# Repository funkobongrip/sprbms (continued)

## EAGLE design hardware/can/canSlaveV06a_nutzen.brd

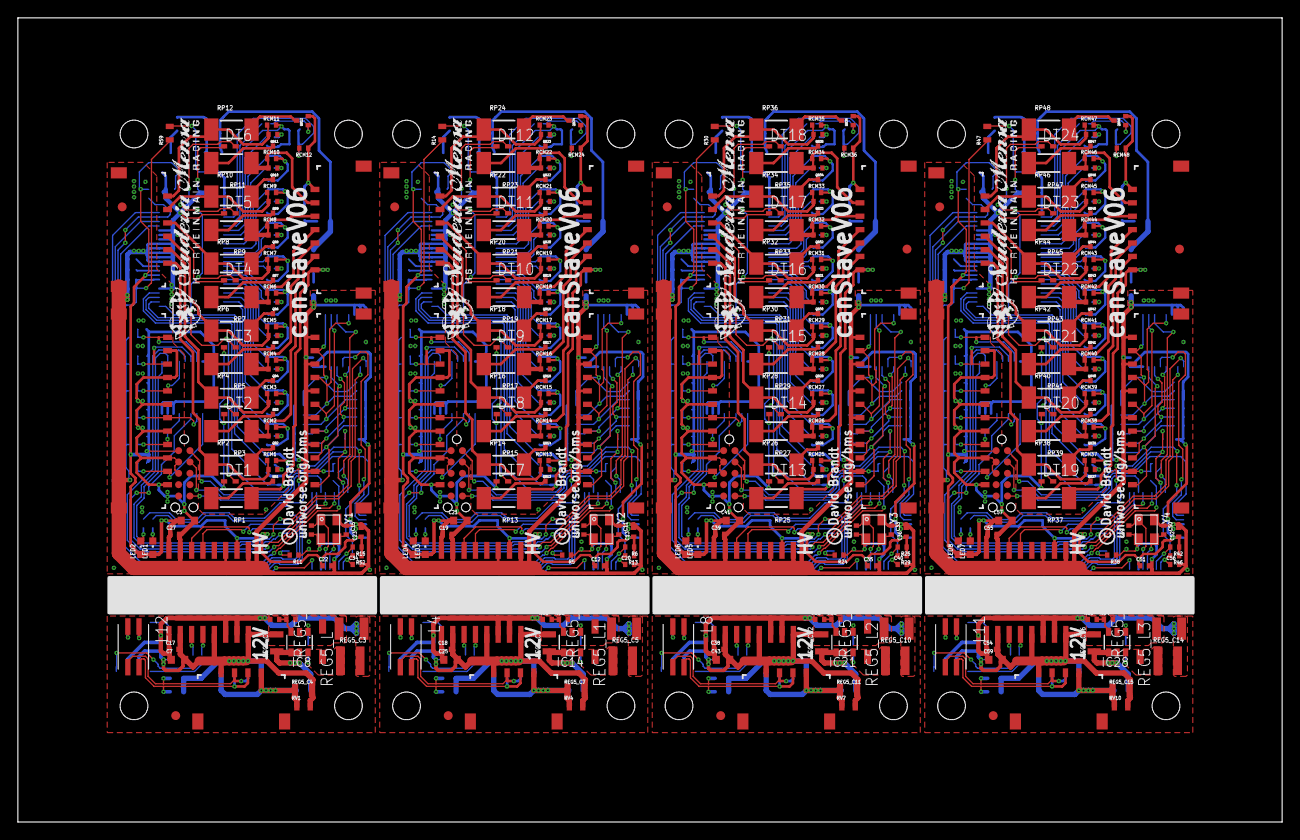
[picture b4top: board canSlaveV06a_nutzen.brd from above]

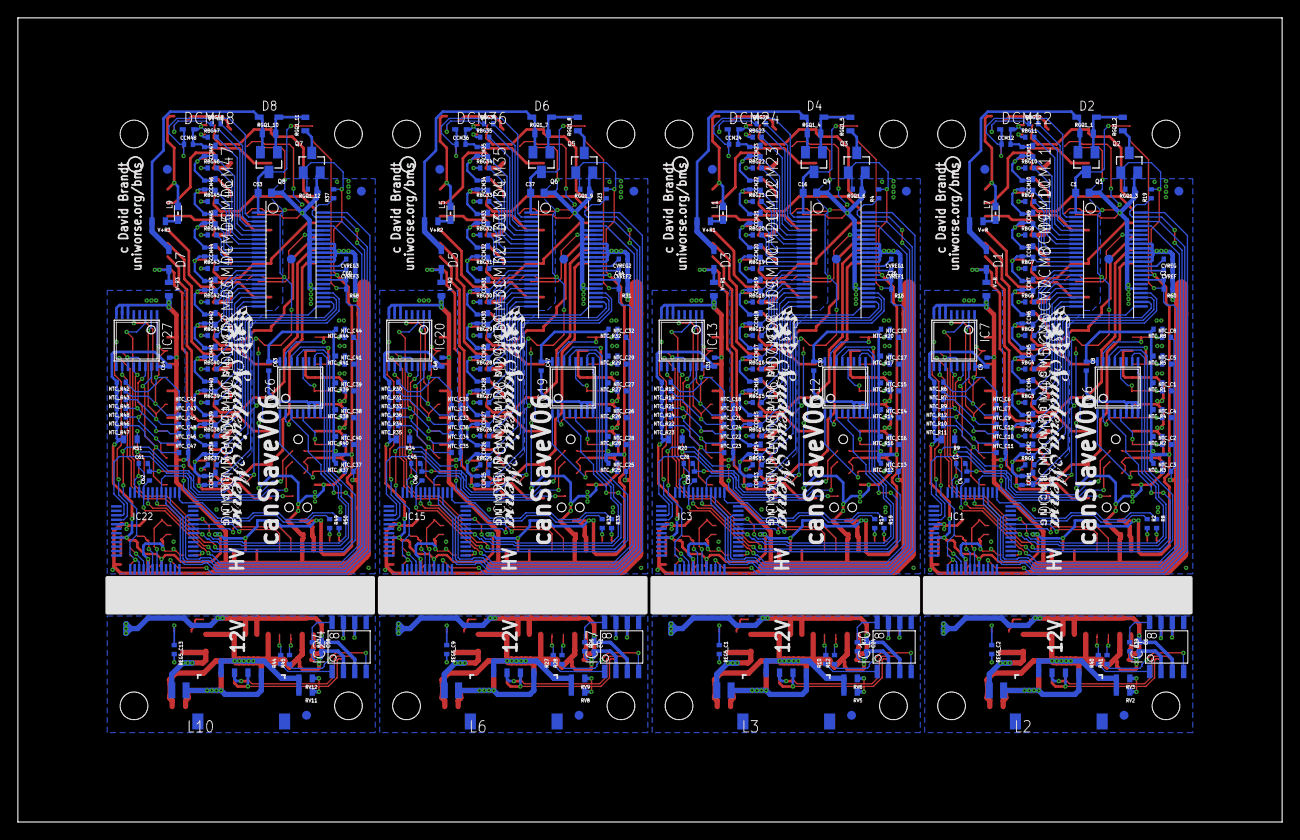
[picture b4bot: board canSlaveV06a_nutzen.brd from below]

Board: 2 copper layers, 141.5 x 90.0 mm, 724 parts (404 on the bottom side), 492 nets.

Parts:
C1, C16, C37, C53: 100n,100V; C0603
C2, C3, C4, C12, C13, C20, C22, C23, C26, C28, C29, C34, C35, C36, C40, C44, C45, C46, C51, C52, C56, C60, C61, C62: 100n; C0402
C5, C7, C21, C25, C41, C43, C57, C59: 10u,10V,X7R; C0603
C6, C8, C9, C17, C18, C19, C24, C27, C30, C31, C38, C39, C42, C47, C48, C54, C55, C58, C63, C64: 100n,>10V,X7R; C0402
C10, C11, C14, C15, C32, C33, C49, C50: 10p; C0402
CCM1, CCM2, CCM3, CCM4, CCM5, CCM6, CCM7, CCM8, CCM9, CCM10, CCM11, CCM12, CCM13, CCM14, CCM15, CCM16, CCM17, CCM18, CCM19, CCM20, CCM21, CCM22, CCM23, CCM24, CCM25, CCM26, CCM27, CCM28, CCM29, CCM30, CCM31, CCM32, CCM33, CCM34, CCM35, CCM36, CCM37, CCM38, CCM39, CCM40, CCM41, CCM42, CCM43, CCM44, CCM45, CCM46, CCM47, CCM48: 100n; C0402
CVREF, CVREF1, CVREF2, CVREF3: 1u; C0402
CVREG, CVREG1, CVREG2, CVREG3: 1u; C0402
D1, D3, D5, D7: 51V; SOD323-L
D2, D4, D6, D8: 12V; SOD323-L
DBG1, DBG2, DBG3, DBG4: JTAG10-TC2050-NL; TC2050-NL-JTORDER
DCM1, DCM2, DCM3, DCM4, DCM5, DCM6, DCM7, DCM8, DCM9, DCM10, DCM11, DCM12, DCM13, DCM14, DCM15, DCM16, DCM17, DCM18, DCM19, DCM20, DCM21, DCM22, DCM23, DCM24, DCM25, DCM26, DCM27, DCM28, DCM29, DCM30, DCM31, DCM32, DCM33, DCM34, DCM35, DCM36, DCM37, DCM38, DCM39, DCM40, DCM41, DCM42, DCM43, DCM44, DCM45, DCM46, DCM47, DCM48: 7.5; SOD523
DT1, DT2, DT3, DT4, DT5, DT6, DT7, DT8, DT9, DT10, DT11, DT12, DT13, DT14, DT15, DT16, DT17, DT18, DT19, DT20, DT21, DT22, DT23, DT24: 1PS79SB40; SOD523
FID1, FID2, FID3, FID4, FID5, FID6, FID7, FID8, FID9, FID10, FID11, FID12, FID13, FID14, FID15, FID16, FID17, FID18, FID19, FID20, FID21, FID22, FID23, FID24, FID25, FID26, FID27, FID28: FIDUCIAL""; FIDUCIAL_1MM
IC1, IC3, IC15, IC22: LPC11C14; LQFP48
IC2, IC9, IC16, IC23: LTC6803-4; 44SSOP
IC4, IC10, IC17, IC24: PCA82C251; SO-8
IC5, IC11, IC18, IC25: ADUM5201; SO16WB
IC6, IC7, IC12, IC13, IC19, IC20, IC26, IC27: 4052-TSSOP16; TSSOP16
IC8, IC14, IC21, IC28: LMR14203; SOT23-6
L1, L5, L7, L9: WE-CBF,742792664; 0603
L2, L3, L6, L10: WE-PMI/74479776233A; WE-PMI_0806
L4, L8, L11, L12: 744242101; WE-SLM
LED1, LED3, LED5, LED7: GRN; CHIPLED_0603
LED2, LED4, LED6, LED8: RED; CHIPLED_0603
NTC_C1, NTC_C2, NTC_C3, NTC_C4, NTC_C5, NTC_C6, NTC_C7, NTC_C8, NTC_C9, NTC_C10, NTC_C11, NTC_C12, NTC_C13, NTC_C14, NTC_C15, NTC_C16, NTC_C17, NTC_C18, NTC_C19, NTC_C20, NTC_C21, NTC_C22, NTC_C23, NTC_C24, NTC_C25, NTC_C26, NTC_C27, NTC_C28, NTC_C29, NTC_C30, NTC_C31, NTC_C32, NTC_C33, NTC_C34, NTC_C35, NTC_C36, NTC_C37, NTC_C38, NTC_C39, NTC_C40, NTC_C41, NTC_C42, NTC_C43, NTC_C44, NTC_C45, NTC_C46, NTC_C47, NTC_C48: 1u; C0402
NTC_R1, NTC_R2, NTC_R3, NTC_R4, NTC_R5, NTC_R6, NTC_R7, NTC_R8, NTC_R9, NTC_R10, NTC_R11, NTC_R12, NTC_R13, NTC_R14, NTC_R15, NTC_R16, NTC_R17, NTC_R18, NTC_R19, NTC_R20, NTC_R21, NTC_R22, NTC_R23, NTC_R24, NTC_R25, NTC_R26, NTC_R27, NTC_R28, NTC_R29, NTC_R30, NTC_R31, NTC_R32, NTC_R33, NTC_R34, NTC_R35, NTC_R36, NTC_R37, NTC_R38, NTC_R39, NTC_R40, NTC_R41, NTC_R42, NTC_R43, NTC_R44, NTC_R45, NTC_R46, NTC_R47, NTC_R48: 10k; R0402
Q1, Q4, Q6, Q8: BSS84; SOT23
Q2, Q3, Q5, Q7: 2N7002; SOT23
QB1, QB2, QB3, QB4, QB5, QB6, QB7, QB8, QB9, QB10, QB11, QB12, QB13, QB14, QB15, QB16, QB17, QB18, QB19, QB20, QB21, QB22, QB23, QB24, QB25, QB26, QB27, QB28, QB29, QB30, QB31, QB32, QB33, QB34, QB35, QB36, QB37, QB38, QB39, QB40, QB41, QB42, QB43, QB44, QB45, QB46, QB47, QB48: BSS84AKT; SOT416
R1, R21, R35, R53: 5.62k; R0402
R2, R8, R17, R18, R32, R33, R49, R50: 1k; R0402
R3, R22, R36, R54: 1.02k; R0402
R4, R19, R23, R37: 4.7k; R0402
R5, R6, R11, R13, R15, R24, R25, R29, R38, R42, R46, R52: 10k; R0402
R7, R26, R39, R43: 0; R0402
R9, R20, R34, R51: 3.3k; R0603
R10, R12, R27, R28, R40, R41, R44, R45: 100; R0402
R14, R30, R47, R59: 332k0.1%; R0603
R16, R31, R48, R60: 20k0.1%; R0402
RBG1, RBG2, RBG3, RBG4, RBG5, RBG6, RBG7, RBG8, RBG9, RBG10, RBG11, RBG12, RBG13, RBG14, RBG15, RBG16, RBG17, RBG18, RBG19, RBG20, RBG21, RBG22, RBG23, RBG24, RBG25, RBG26, RBG27, RBG28, RBG29, RBG30, RBG31, RBG32, RBG33, RBG34, RBG35, RBG36, RBG37, RBG38, RBG39, RBG40, RBG41, RBG42, RBG43, RBG44, RBG45, RBG46, RBG47, RBG48: 3.3k; R0402
RCM1, RCM2, RCM3, RCM4, RCM5, RCM6, RCM7, RCM8, RCM9, RCM10, RCM11, RCM12, RCM13, RCM14, RCM15, RCM16, RCM17, RCM18, RCM19, RCM20, RCM21, RCM22, RCM23, RCM24, RCM25, RCM26, RCM27, RCM28, RCM29, RCM30, RCM31, RCM32, RCM33, RCM34, RCM35, RCM36, RCM37, RCM38, RCM39, RCM40, RCM41, RCM42, RCM43, RCM44, RCM45, RCM46, RCM47, RCM48: 100; R0402
REG5_C1, REG5_C2, REG5_C9, REG5_C13: 100n,>=25V,>=X5R; C0402
REG5_C3, REG5_C5, REG5_C10, REG5_C14: 47u,10V,X7R; C1210
REG5_C4, REG5_C6, REG5_C7, REG5_C8, REG5_C11, REG5_C12, REG5_C15, REG5_C16: 2.2u,50V,X7R; C0805
REG5_D1, REG5_D2, REG5_D3, REG5_D4: PMEG6010CEH; SOD123
REG5_L, REG5_L1, REG5_L2, REG5_L3: 744025100; WE-TPC_2828
RGQ1_1, RGQ1_4, RGQ1_7, RGQ1_10: 1M,50V; R0603
RGQ1_2, RGQ1_5, RGQ1_8, RGQ1_11: 100k,50V; R0603
RGQ1_3, RGQ1_6, RGQ1_9, RGQ1_12: 1M; R0402
RP1, RP2, RP3, RP4, RP5, RP6, RP7, RP8, RP9, RP10, RP11, RP12, RP13, RP14, RP15, RP16, RP17, RP18, RP19, RP20, RP21, RP22, RP23, RP24, RP25, RP26, RP27, RP28, RP29, RP30, RP31, RP32, RP33, RP34, RP35, RP36, RP37, RP38, RP39, RP40, RP41, RP42, RP43, RP44, RP45, RP46, RP47, RP48: 22; MINI_MELF-0207R
RV1, RV2, RV3, RV4, RV5, RV6, RV7, RV8, RV9, RV10, RV11, RV12: 24V; R0603
U$1, U$3, U$5, U$7: SMLOGOS_BSILK
U$2, U$4, U$6, U$8: SMLOGOS_SILK
V+R, V+R1, V+R2, V+R3: 100; R0603
V-R, V-R1, V-R2, V-R3: 100; R0603
X1, X8, X14, X20: 504050-0791
X2, X7, X13, X19: 504050-0691
X3, X4, X11, X12, X17, X18, X23, X24: 504050-0491
X5, X6, X9, X10, X15, X16, X21, X22: 504050-1291
Y1, Y2, Y3, Y4: 12Mhz; MT

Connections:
!RESET: C34.1, DBG1.10, IC1.3, R52.2
!RESET1: C20.1, DBG2.10, IC3.3, R13.2
!RESET2: C40.1, DBG3.10, IC15.3, R29.2
!RESET3: C56.1, DBG4.10, IC22.3, R46.2
+3V1: C12.1, C13.1, C19.1, C21.1, C30.1, C31.1, DBG2.1, IC3.8, IC3.44, IC9.30, IC11.P$10, IC11.P$16, IC12.16, IC13.16, LED3.A, LED4.A, NTC_R13.2, NTC_R14.2, NTC_R15.2, NTC_R16.2, NTC_R17.2, NTC_R18.2, NTC_R19.2, NTC_R20.2, NTC_R21.2, NTC_R22.2, NTC_R23.2, NTC_R24.2, Q3.1, R4.2, R6.1, R13.1, R20.2, RGQ1_6.2
+3V2: C35.1, C36.1, C39.1, C41.1, C47.1, C48.1, DBG3.1, IC15.8, IC15.44, IC16.30, IC18.P$10, IC18.P$16, IC19.16, IC20.16, LED5.A, LED6.A, NTC_R25.2, NTC_R26.2, NTC_R27.2, NTC_R28.2, NTC_R29.2, NTC_R30.2, NTC_R31.2, NTC_R32.2, NTC_R33.2, NTC_R34.2, NTC_R35.2, NTC_R36.2, Q5.1, R23.2, R25.1, R29.1, R34.2, RGQ1_9.2
+3V3: C5.1, C8.1, C9.1, C22.1, C23.1, C27.1, DBG1.1, IC1.8, IC1.44, IC2.30, IC5.P$10, IC5.P$16, IC6.16, IC7.16, LED1.A, LED2.A, NTC_R1.2, NTC_R2.2, NTC_R3.2, NTC_R4.2, NTC_R5.2, NTC_R6.2, NTC_R7.2, NTC_R8.2, NTC_R9.2, NTC_R10.2, NTC_R11.2, NTC_R12.2, Q2.1, R9.2, R15.1, R19.2, R52.1, RGQ1_3.2
+3V4: C51.1, C52.1, C55.1, C57.1, C63.1, C64.1, DBG4.1, IC22.8, IC22.44, IC23.30, IC25.P$10, IC25.P$16, IC26.16, IC27.16, LED7.A, LED8.A, NTC_R37.2, NTC_R38.2, NTC_R39.2, NTC_R40.2, NTC_R41.2, NTC_R42.2, NTC_R43.2, NTC_R44.2, NTC_R45.2, NTC_R46.2, NTC_R47.2, NTC_R48.2, Q7.1, R37.2, R42.1, R46.1, R51.2, RGQ1_12.2
BAL1: IC2.25, RBG1.2
BAL2: IC2.23, RBG2.2
BAL3: IC2.21, RBG3.2
BAL4: IC2.19, RBG4.2
BAL5: IC2.17, RBG5.2
BAL6: IC2.15, RBG6.2
BAL7: IC2.13, RBG7.2
BAL8: IC2.11, RBG8.2
BAL9: IC2.9, RBG9.2
BAL10: IC2.7, RBG10.2
BAL11: IC2.5, RBG11.2
BAL12: IC2.3, RBG12.2
BAL13: IC9.25, RBG13.2
BAL14: IC9.23, RBG14.2
BAL15: IC9.21, RBG15.2
BAL16: IC9.19, RBG16.2
BAL17: IC9.17, RBG17.2
BAL18: IC9.15, RBG18.2
BAL19: IC9.13, RBG19.2
BAL20: IC9.11, RBG20.2
BAL21: IC9.9, RBG21.2
BAL22: IC9.7, RBG22.2
BAL23: IC9.5, RBG23.2
BAL24: IC9.3, RBG24.2
BAL25: IC16.25, RBG25.2
BAL26: IC16.23, RBG26.2
BAL27: IC16.21, RBG27.2
BAL28: IC16.19, RBG28.2
BAL29: IC16.17, RBG29.2
BAL30: IC16.15, RBG30.2
BAL31: IC16.13, RBG31.2
BAL32: IC16.11, RBG32.2
BAL33: IC16.9, RBG33.2
BAL34: IC16.7, RBG34.2
BAL35: IC16.5, RBG35.2
BAL36: IC16.3, RBG36.2
BAL37: IC23.25, RBG37.2
BAL38: IC23.23, RBG38.2
BAL39: IC23.21, RBG39.2
BAL40: IC23.19, RBG40.2
BAL41: IC23.17, RBG41.2
BAL42: IC23.15, RBG42.2
BAL43: IC23.13, RBG43.2
BAL44: IC23.11, RBG44.2
BAL45: IC23.9, RBG45.2
BAL46: IC23.7, RBG46.2
BAL47: IC23.5, RBG47.2
BAL48: IC23.3, RBG48.2
BOOST1: IC8.1, REG5_C2.1
BOOST2: IC14.1, REG5_C1.1
BOOST3: IC21.1, REG5_C9.1
BOOST4: IC28.1, REG5_C13.1
C0: CCM1.2, D1.A, DCM1.A, IC2.26, RP1.1, V-R.1, X1.7
C1: QB1.2, RCM1.1, RP2.1, X2.1
C1M: CCM1.1, CCM2.2, DCM1.C, DCM2.A, IC2.24, RCM1.2
C1M1: CCM13.1, CCM14.2, DCM13.C, DCM14.A, IC9.24, RCM13.2
C1M2: CCM25.1, CCM26.2, DCM25.C, DCM26.A, IC16.24, RCM25.2
C1M3: CCM37.1, CCM38.2, DCM37.C, DCM38.A, IC23.24, RCM37.2
C2: QB2.2, RCM2.1, RP3.1, X1.6
C2M: CCM2.1, CCM3.2, DCM2.C, DCM3.A, IC2.22, RCM2.2
C2M1: CCM14.1, CCM15.2, DCM14.C, DCM15.A, IC9.22, RCM14.2
C2M2: CCM26.1, CCM27.2, DCM26.C, DCM27.A, IC16.22, RCM26.2
C2M3: CCM38.1, CCM39.2, DCM38.C, DCM39.A, IC23.22, RCM38.2
C3: QB3.2, RCM3.1, RP4.1, X2.2
C3M: CCM3.1, CCM4.2, DCM3.C, DCM4.A, IC2.20, RCM3.2
C3M1: CCM15.1, CCM16.2, DCM15.C, DCM16.A, IC9.20, RCM15.2
C3M2: CCM27.1, CCM28.2, DCM27.C, DCM28.A, IC16.20, RCM27.2
C3M3: CCM39.1, CCM40.2, DCM39.C, DCM40.A, IC23.20, RCM39.2
C4: QB4.2, RCM4.1, RP5.1, X1.5
C4M: CCM4.1, CCM5.2, DCM4.C, DCM5.A, IC2.18, RCM4.2
C4M1: CCM16.1, CCM17.2, DCM16.C, DCM17.A, IC9.18, RCM16.2
C4M2: CCM28.1, CCM29.2, DCM28.C, DCM29.A, IC16.18, RCM28.2
C4M3: CCM40.1, CCM41.2, DCM40.C, DCM41.A, IC23.18, RCM40.2
C5: QB5.2, RCM5.1, RP6.1, X2.3
C5M: CCM5.1, CCM6.2, DCM5.C, DCM6.A, IC2.16, RCM5.2
C5M1: CCM17.1, CCM18.2, DCM17.C, DCM18.A, IC9.16, RCM17.2
C5M2: CCM29.1, CCM30.2, DCM29.C, DCM30.A, IC16.16, RCM29.2
C5M3: CCM41.1, CCM42.2, DCM41.C, DCM42.A, IC23.16, RCM41.2
C6: QB6.2, RCM6.1, RP7.1, X1.4
C6M: CCM6.1, CCM7.2, DCM6.C, DCM7.A, IC2.14, RCM6.2
C6M1: CCM18.1, CCM19.2, DCM18.C, DCM19.A, IC9.14, RCM18.2
C6M2: CCM30.1, CCM31.2, DCM30.C, DCM31.A, IC16.14, RCM30.2
C6M3: CCM42.1, CCM43.2, DCM42.C, DCM43.A, IC23.14, RCM42.2
C7: QB7.2, RCM7.1, RP8.1, X2.4
C7M: CCM7.1, CCM8.2, DCM7.C, DCM8.A, IC2.12, RCM7.2
C7M1: CCM19.1, CCM20.2, DCM19.C, DCM20.A, IC9.12, RCM19.2
C7M2: CCM31.1, CCM32.2, DCM31.C, DCM32.A, IC16.12, RCM31.2
C7M3: CCM43.1, CCM44.2, DCM43.C, DCM44.A, IC23.12, RCM43.2
C8: QB8.2, RCM8.1, RP9.1, X1.3
C8M: CCM8.1, CCM9.2, DCM8.C, DCM9.A, IC2.10, RCM8.2
C8M1: CCM20.1, CCM21.2, DCM20.C, DCM21.A, IC9.10, RCM20.2
C8M2: CCM32.1, CCM33.2, DCM32.C, DCM33.A, IC16.10, RCM32.2
C8M3: CCM44.1, CCM45.2, DCM44.C, DCM45.A, IC23.10, RCM44.2
C9: QB9.2, RCM9.1, RP10.1, X2.5
C9M: CCM9.1, CCM10.2, DCM9.C, DCM10.A, IC2.8, RCM9.2
C9M1: CCM21.1, CCM22.2, DCM21.C, DCM22.A, IC9.8, RCM21.2
C9M2: CCM33.1, CCM34.2, DCM33.C, DCM34.A, IC16.8, RCM33.2
C9M3: CCM45.1, CCM46.2, DCM45.C, DCM46.A, IC23.8, RCM45.2
C10: QB10.2, RCM10.1, RP11.1, X1.2
C10M: CCM10.1, CCM11.2, DCM10.C, DCM11.A, IC2.6, RCM10.2
C10M1: CCM22.1, CCM23.2, DCM22.C, DCM23.A, IC9.6, RCM22.2
C10M2: CCM34.1, CCM35.2, DCM34.C, DCM35.A, IC16.6, RCM34.2
C10M3: CCM46.1, CCM47.2, DCM46.C, DCM47.A, IC23.6, RCM46.2
C11: QB11.2, RCM11.1, RP12.1, X2.6
C11M: CCM11.1, CCM12.2, DCM11.C, DCM12.A, IC2.4, RCM11.2
C11M1: CCM23.1, CCM24.2, DCM23.C, DCM24.A, IC9.4, RCM23.2
C11M2: CCM35.1, CCM36.2, DCM35.C, DCM36.A, IC16.4, RCM35.2
C11M3: CCM47.1, CCM48.2, DCM47.C, DCM48.A, IC23.4, RCM47.2
C12: L7.1, QB12.2, RCM12.1, X1.1
C12FILT: L7.2, V+R.1
C12FILT1: L1.2, V+R1.1
C12FILT2: L5.2, V+R2.1
C12FILT3: L9.2, V+R3.1
C12M: CCM12.1, DCM12.C, IC2.2, RCM12.2
C12M1: CCM24.1, DCM24.C, IC9.2, RCM24.2
C12M2: CCM36.1, DCM36.C, IC16.2, RCM36.2
C12M3: CCM48.1, DCM48.C, IC23.2, RCM48.2
C13: CCM13.2, D3.A, DCM13.A, IC9.26, RP13.1, V-R1.1, X8.7
C14: QB20.2, RCM20.1, RP21.1, X8.3
C15: QB14.2, RCM14.1, RP15.1, X8.6
C16: QB13.2, RCM13.1, RP14.1, X7.1
C17: QB15.2, RCM15.1, RP16.1, X7.2
C18: QB16.2, RCM16.1, RP17.1, X8.5
C19: QB17.2, RCM17.1, RP18.1, X7.3
C20: QB18.2, RCM18.1, RP19.1, X8.4
C21: QB19.2, RCM19.1, RP20.1, X7.4
C22: QB21.2, RCM21.1, RP22.1, X7.5
C23: QB22.2, RCM22.1, RP23.1, X8.2
C24: QB23.2, RCM23.1, RP24.1, X7.6
C25: L1.1, QB24.2, RCM24.1, X8.1
C26: CCM25.2, D5.A, DCM25.A, IC16.26, RP25.1, V-R2.1, X14.7
C27: QB32.2, RCM32.1, RP33.1, X14.3
C28: QB26.2, RCM26.1, RP27.1, X14.6
C29: QB25.2, RCM25.1, RP26.1, X13.1
C30: QB27.2, RCM27.1, RP28.1, X13.2
C31: QB28.2, RCM28.1, RP29.1, X14.5
C32: QB29.2, RCM29.1, RP30.1, X13.3
C33: QB30.2, RCM30.1, RP31.1, X14.4
C34: QB31.2, RCM31.1, RP32.1, X13.4
C35: QB33.2, RCM33.1, RP34.1, X13.5
C36: QB34.2, RCM34.1, RP35.1, X14.2
C37: QB35.2, RCM35.1, RP36.1, X13.6
C38: L5.1, QB36.2, RCM36.1, X14.1
C39: CCM37.2, D7.A, DCM37.A, IC23.26, RP37.1, V-R3.1, X20.7
C40: QB44.2, RCM44.1, RP45.1, X20.3
C41: QB38.2, RCM38.1, RP39.1, X20.6
C42: QB37.2, RCM37.1, RP38.1, X19.1
C43: QB39.2, RCM39.1, RP40.1, X19.2
C44: QB40.2, RCM40.1, RP41.1, X20.5
C45: QB41.2, RCM41.1, RP42.1, X19.3
C46: QB42.2, RCM42.1, RP43.1, X20.4
C47: QB43.2, RCM43.1, RP44.1, X19.4
C48: QB45.2, RCM45.1, RP46.1, X19.5
C49: QB46.2, RCM46.1, RP47.1, X20.2
C50: QB47.2, RCM47.1, RP48.1, X19.6
C51: L9.1, QB48.2, RCM48.1, X20.1
CANH: L12.4, RV2.1, X3.2, X4.2
CANH1: L4.4, RV5.1, X11.2, X12.2
CANH2: L8.4, RV8.1, X17.2, X18.2
CANH3: L11.4, RV11.1, X23.2, X24.2
CANL: L12.3, RV3.1, X3.3, X4.3
CANL1: L4.3, RV6.1, X11.3, X12.3
CANL2: L8.3, RV9.1, X17.3, X18.3
CANL3: L11.3, RV12.1, X23.3, X24.3
CANRX: IC1.19, IC5.P$14
CANRX1: IC3.19, IC11.P$14
CANRX2: IC15.19, IC18.P$14
CANRX3: IC22.19, IC25.P$14
CANTX: IC1.20, IC5.P$13
CANTX1: IC3.20, IC11.P$13
CANTX2: IC15.20, IC18.P$13
CANTX3: IC22.20, IC25.P$13
CAR+5V: C6.1, C7.1, C17.1, IC4.3, IC5.P$1, IC5.P$6, IC5.P$7, R1.1, REG5_C3.1, REG5_L.2
CAR+5V1: C18.1, C24.1, C25.1, IC10.3, IC11.P$1, IC11.P$6, IC11.P$7, R21.1, REG5_C5.1, REG5_L1.2
CAR+5V2: C38.1, C42.1, C43.1, IC17.3, IC18.P$1, IC18.P$6, IC18.P$7, R35.1, REG5_C10.1, REG5_L2.2
CAR+5V3: C54.1, C58.1, C59.1, IC24.3, IC25.P$1, IC25.P$6, IC25.P$7, R53.1, REG5_C14.1, REG5_L3.2
CARGND: C6.2, C7.2, C17.2, IC4.2, IC5.P$2, IC5.P$5, IC5.P$8, IC8.2, R3.2, R39.2, REG5_C3.2, REG5_C4.2, REG5_C6.2, REG5_D2.2, RV1.2, RV2.2, RV3.2, X3.4, X4.4
CARGND1: C18.2, C24.2, C25.2, IC10.2, IC11.P$2, IC11.P$5, IC11.P$8, IC14.2, R7.2, R22.2, REG5_C5.2, REG5_C7.2, REG5_C8.2, REG5_D1.2, RV4.2, RV5.2, RV6.2, X11.4, X12.4
CARGND2: C38.2, C42.2, C43.2, IC17.2, IC18.P$2, IC18.P$5, IC18.P$8, IC21.2, R26.2, R36.2, REG5_C10.2, REG5_C11.2, REG5_C12.2, REG5_D3.2, RV7.2, RV8.2, RV9.2, X17.4, X18.4
CARGND3: C54.2, C58.2, C59.2, IC24.2, IC25.P$2, IC25.P$5, IC25.P$8, IC28.2, R43.2, R54.2, REG5_C14.2, REG5_C15.2, REG5_C16.2, REG5_D4.2, RV10.2, RV11.2, RV12.2, X23.4, X24.4
CARVIN: L2.1, REG5_C4.1, RV1.1, X3.1, X4.1
CARVIN1: L3.1, REG5_C7.1, RV4.1, X11.1, X12.1
CARVIN2: L6.1, REG5_C11.1, RV7.1, X17.1, X18.1
CARVIN3: L10.1, REG5_C15.1, RV10.1, X23.1, X24.1
CARVINFILT: IC8.4, IC8.5, L2.2, REG5_C6.1
CARVINFILT1: IC14.4, IC14.5, L3.2, REG5_C8.1
CARVINFILT2: IC21.4, IC21.5, L6.2, REG5_C12.1
CARVINFILT3: IC28.4, IC28.5, L10.2, REG5_C16.1
CAR_CANRX: IC5.P$3, R41.2
CAR_CANRX1: IC11.P$3, R12.2
CAR_CANRX2: IC18.P$3, R28.2
CAR_CANRX3: IC25.P$3, R45.2
CAR_CANRX_T: IC4.4, R41.1
CAR_CANRX_T1: IC10.4, R12.1
CAR_CANRX_T2: IC17.4, R28.1
CAR_CANRX_T3: IC24.4, R45.1
CAR_CANTX: IC5.P$4, R40.2
CAR_CANTX1: IC11.P$4, R10.2
CAR_CANTX2: IC18.P$4, R27.2
CAR_CANTX3: IC25.P$4, R44.2
CAR_CANTX_T: IC4.1, R40.1
CAR_CANTX_T1: IC10.1, R10.1
CAR_CANTX_T2: IC17.1, R27.1
CAR_CANTX_T3: IC24.1, R44.1
CR1: QB1.3, RP1.2
CR2: QB2.3, RP2.2
CR3: QB3.3, RP3.2
CR4: QB4.3, RP4.2
CR5: QB5.3, RP5.2
CR6: QB6.3, RP6.2
CR7: QB7.3, RP7.2
CR8: QB8.3, RP8.2
CR9: QB9.3, RP9.2
CR10: QB10.3, RP10.2
CR11: QB11.3, RP11.2
CR12: QB12.3, RP12.2
CR13: QB13.3, RP13.2
CR14: QB14.3, RP14.2
CR15: QB15.3, RP15.2
CR16: QB16.3, RP16.2
CR17: QB17.3, RP17.2
CR18: QB18.3, RP18.2
CR19: QB19.3, RP19.2
CR20: QB20.3, RP20.2
CR21: QB21.3, RP21.2
CR22: QB22.3, RP22.2
CR23: QB23.3, RP23.2
CR24: QB24.3, RP24.2
CR25: QB25.3, RP25.2
CR26: QB26.3, RP26.2
CR27: QB27.3, RP27.2
CR28: QB28.3, RP28.2
CR29: QB29.3, RP29.2
CR30: QB30.3, RP30.2
CR31: QB31.3, RP31.2
CR32: QB32.3, RP32.2
CR33: QB33.3, RP33.2
CR34: QB34.3, RP34.2
CR35: QB35.3, RP35.2
CR36: QB36.3, RP36.2
CR37: QB37.3, RP37.2
CR38: QB38.3, RP38.2
CR39: QB39.3, RP39.2
CR40: QB40.3, RP40.2
CR41: QB41.3, RP41.2
CR42: QB42.3, RP42.2
CR43: QB43.3, RP43.2
CR44: QB44.3, RP44.2
CR45: QB45.3, RP45.2
CR46: QB46.3, RP46.2
CR47: QB47.3, RP47.2
CR48: QB48.3, RP48.2
FSM: C2.1, C4.1, IC1.33, IC2.29, R59.1, R60.2
FSM1: C26.1, C29.1, IC3.33, IC9.29, R14.1, R16.2
FSM2: C44.1, C46.1, IC15.33, IC16.29, R30.1, R31.2
FSM3: C60.1, C62.1, IC22.33, IC23.29, R47.1, R48.2
GND: C1.2, C2.2, C3.2, C4.2, C5.2, C8.2, C9.2, C14.1, C15.1, C22.2, C23.2, C27.2, C34.2, CVREF.1, CVREG.1, DBG1.3, DBG1.5, DT1.C, DT2.C, DT3.C, DT4.C, DT5.C, DT6.C, IC1.5, IC1.41, IC2.27, IC2.33, IC2.34, IC2.35, IC2.36, IC2.37, IC2.38, IC2.39, IC2.40, IC5.P$9, IC5.P$11, IC5.P$15, IC6.6, IC6.7, IC6.8, IC7.6, IC7.7, IC7.8, NTC_C1.2, NTC_C2.2, NTC_C3.2, NTC_C4.2, NTC_C5.2, NTC_C6.2, NTC_C7.2, NTC_C8.2, NTC_C9.2, NTC_C10.2, NTC_C11.2, NTC_C12.2, Q2.2, R11.1, R60.1, RGQ1_3.1, V-R.2, X2.P1, X5.1, X5.3, X5.5, X5.7, X5.9, X5.11, X5.P1, X5.P2, X6.1, X6.3, X6.5, X6.7, X6.9, X6.11, Y1.P2, Y1.P4
GND1: C10.1, C11.1, C12.2, C13.2, C16.2, C19.2, C20.2, C21.2, C26.2, C28.2, C29.2, C30.2, C31.2, CVREF1.1, CVREG1.1, DBG2.3, DBG2.5, DT7.C, DT8.C, DT9.C, DT10.C, DT11.C, DT12.C, IC3.5, IC3.41, IC9.27, IC9.33, IC9.34, IC9.35, IC9.36, IC9.37, IC9.38, IC9.39, IC9.40, IC11.P$9, IC11.P$11, IC11.P$15, IC12.6, IC12.7, IC12.8, IC13.6, IC13.7, IC13.8, NTC_C13.2, NTC_C14.2, NTC_C15.2, NTC_C16.2, NTC_C17.2, NTC_C18.2, NTC_C19.2, NTC_C20.2, NTC_C21.2, NTC_C22.2, NTC_C23.2, NTC_C24.2, Q3.2, R5.1, R16.1, RGQ1_6.1, V-R1.2, X7.P1, X9.1, X9.3, X9.5, X9.7, X9.9, X9.11, X9.P1, X9.P2, X10.1, X10.3, X10.5, X10.7, X10.9, X10.11, Y2.P2, Y2.P4
GND2: C32.1, C33.1, C35.2, C36.2, C37.2, C39.2, C40.2, C41.2, C44.2, C45.2, C46.2, C47.2, C48.2, CVREF2.1, CVREG2.1, DBG3.3, DBG3.5, DT13.C, DT14.C, DT15.C, DT16.C, DT17.C, DT18.C, IC15.5, IC15.41, IC16.27, IC16.33, IC16.34, IC16.35, IC16.36, IC16.37, IC16.38, IC16.39, IC16.40, IC18.P$9, IC18.P$11, IC18.P$15, IC19.6, IC19.7, IC19.8, IC20.6, IC20.7, IC20.8, NTC_C25.2, NTC_C26.2, NTC_C27.2, NTC_C28.2, NTC_C29.2, NTC_C30.2, NTC_C31.2, NTC_C32.2, NTC_C33.2, NTC_C34.2, NTC_C35.2, NTC_C36.2, Q5.2, R24.1, R31.1, RGQ1_9.1, V-R2.2, X13.P1, X15.1, X15.3, X15.5, X15.7, X15.9, X15.11, X15.P1, X15.P2, X16.1, X16.3, X16.5, X16.7, X16.9, X16.11, Y3.P2, Y3.P4
GND3: C49.1, C50.1, C51.2, C52.2, C53.2, C55.2, C56.2, C57.2, C60.2, C61.2, C62.2, C63.2, C64.2, CVREF3.1, CVREG3.1, DBG4.3, DBG4.5, DT19.C, DT20.C, DT21.C, DT22.C, DT23.C, DT24.C, IC22.5, IC22.41, IC23.27, IC23.33, IC23.34, IC23.35, IC23.36, IC23.37, IC23.38, IC23.39, IC23.40, IC25.P$9, IC25.P$11, IC25.P$15, IC26.6, IC26.7, IC26.8, IC27.6, IC27.7, IC27.8, NTC_C37.2, NTC_C38.2, NTC_C39.2, NTC_C40.2, NTC_C41.2, NTC_C42.2, NTC_C43.2, NTC_C44.2, NTC_C45.2, NTC_C46.2, NTC_C47.2, NTC_C48.2, Q7.2, R38.1, R48.1, RGQ1_12.1, V-R3.2, X19.P1, X21.1, X21.3, X21.5, X21.7, X21.9, X21.11, X21.P1, X21.P2, X22.1, X22.3, X22.5, X22.7, X22.9, X22.11, Y4.P2, Y4.P4
ISP_CAN: IC1.14, R11.2
ISP_CAN1: IC3.14, R5.2
ISP_CAN2: IC15.14, R24.2
ISP_CAN3: IC22.14, R38.2
ISP_ENTER: IC1.4, R15.2
ISP_ENTER1: IC3.4, R6.2
ISP_ENTER2: IC15.4, R25.2
ISP_ENTER3: IC22.4, R42.2
LED1: IC1.24, R2.1
LED1C: LED1.C, R2.2
LED1C1: LED3.C, R17.2
LED1C2: LED5.C, R32.2
LED1C3: LED7.C, R49.2
LED2: IC1.25, R8.1
LED2C: LED2.C, R8.2
LED2C1: LED4.C, R18.2
LED2C2: LED6.C, R33.2
LED2C3: LED8.C, R50.2
LED3: IC3.24, R17.1
LED4: IC3.25, R18.1
LED5: IC15.24, R32.1
LED6: IC15.25, R33.1
LED7: IC22.24, R49.1
LED8: IC22.25, R50.1
MISO0: IC1.27, IC2.43, R19.1
MISO3: IC3.27, IC9.43, R4.1
MISO5: IC15.27, IC16.43, R23.1
MISO7: IC22.27, IC23.43, R37.1
MOSI0: IC1.28, IC2.42
MOSI3: IC3.28, IC9.42
MOSI5: IC15.28, IC16.42
MOSI7: IC22.28, IC23.42
unnamed: IC8.3, R1.2, R3.1
unnamed: IC4.7, L12.1
unnamed: IC10.7, L4.1
unnamed: IC10.6, L4.2
unnamed: IC14.3, R21.2, R22.1
unnamed: IC4.6, L12.2
unnamed: IC17.7, L8.1
unnamed: IC17.6, L8.2
unnamed: IC21.3, R35.2, R36.1
unnamed: IC24.7, L11.1
unnamed: IC24.6, L11.2
unnamed: IC28.3, R53.2, R54.1
Q1G: D2.A, Q1.1, RGQ1_1.2, RGQ1_2.2
Q1G1: D4.A, Q4.1, RGQ1_4.2, RGQ1_5.2
Q1G2: D6.A, Q6.1, RGQ1_7.2, RGQ1_8.2
Q1G3: D8.A, Q8.1, RGQ1_10.2, RGQ1_11.2
Q1GR: Q2.3, RGQ1_2.1
Q1GR1: Q3.3, RGQ1_5.1
Q1GR2: Q5.3, RGQ1_8.1
Q1GR3: Q7.3, RGQ1_11.1
QBG1: QB1.1, RBG1.1
QBG2: QB2.1, RBG2.1
QBG3: QB3.1, RBG3.1
QBG4: QB4.1, RBG4.1
QBG5: QB5.1, RBG5.1
QBG6: QB6.1, RBG6.1
QBG7: QB7.1, RBG7.1
QBG8: QB8.1, RBG8.1
QBG9: QB9.1, RBG9.1
QBG10: QB10.1, RBG10.1
QBG11: QB11.1, RBG11.1
QBG12: QB12.1, RBG12.1
QBG13: QB13.1, RBG13.1
QBG14: QB14.1, RBG14.1
QBG15: QB15.1, RBG15.1
QBG16: QB16.1, RBG16.1
QBG17: QB17.1, RBG17.1
QBG18: QB18.1, RBG18.1
QBG19: QB19.1, RBG19.1
QBG20: QB20.1, RBG20.1
QBG21: QB21.1, RBG21.1
QBG22: QB22.1, RBG22.1
QBG23: QB23.1, RBG23.1
QBG24: QB24.1, RBG24.1
QBG25: QB25.1, RBG25.1
QBG26: QB26.1, RBG26.1
QBG27: QB27.1, RBG27.1
QBG28: QB28.1, RBG28.1
QBG29: QB29.1, RBG29.1
QBG30: QB30.1, RBG30.1
QBG31: QB31.1, RBG31.1
QBG32: QB32.1, RBG32.1
QBG33: QB33.1, RBG33.1
QBG34: QB34.1, RBG34.1
QBG35: QB35.1, RBG35.1
QBG36: QB36.1, RBG36.1
QBG37: QB37.1, RBG37.1
QBG38: QB38.1, RBG38.1
QBG39: QB39.1, RBG39.1
QBG40: QB40.1, RBG40.1
QBG41: QB41.1, RBG41.1
QBG42: QB42.1, RBG42.1
QBG43: QB43.1, RBG43.1
QBG44: QB44.1, RBG44.1
QBG45: QB45.1, RBG45.1
QBG46: QB46.1, RBG46.1
QBG47: QB47.1, RBG47.1
QBG48: QB48.1, RBG48.1
RS1: IC4.8, R39.1
RS2: IC10.8, R7.1
RS3: IC17.8, R26.1
RS4: IC24.8, R43.1
SCK0: IC1.22, IC2.41
SCK3: IC3.22, IC9.41
SCK5: IC15.22, IC16.41
SCK7: IC22.22, IC23.41
SSEL0: IC1.10, IC2.44
SSEL3: IC3.10, IC9.44
SSEL5: IC15.10, IC16.44
SSEL7: IC22.10, IC23.44
SW1: IC8.6, REG5_C2.2, REG5_D2.1, REG5_L.1
SW2: IC14.6, REG5_C1.2, REG5_D1.1, REG5_L1.1
SW3: IC21.6, REG5_C9.2, REG5_D3.1, REG5_L2.1
SW4: IC28.6, REG5_C13.2, REG5_D4.1, REG5_L3.1
SWCLK: DBG1.4, IC1.29
SWCLK1: DBG2.4, IC3.29
SWCLK2: DBG3.4, IC15.29
SWCLK3: DBG4.4, IC22.29
SWDIO: DBG1.2, IC1.39
SWDIO1: DBG2.2, IC3.39
SWDIO2: DBG3.2, IC15.39
SWDIO3: DBG4.2, IC22.39
TEMP0: IC6.1, NTC_C3.1, NTC_R3.1, X5.2
TEMP1: IC6.5, NTC_C2.1, NTC_R2.1, X5.4
TEMP2: IC6.2, NTC_C4.1, NTC_R4.1, X5.6
TEMP3: IC6.12, NTC_C1.1, NTC_R1.1, X5.8
TEMP4: IC6.14, NTC_C5.1, NTC_R5.1, X5.10
TEMP5: IC6.15, NTC_C8.1, NTC_R8.1, X5.12
TEMP6: IC7.1, NTC_C6.1, NTC_R6.1, X6.2
TEMP7: IC7.5, NTC_C7.1, NTC_R7.1, X6.4
TEMP8: IC7.2, NTC_C9.1, NTC_R9.1, X6.6
TEMP9: IC7.12, NTC_C12.1, NTC_R12.1, X6.8
TEMP10: IC7.14, NTC_C10.1, NTC_R10.1, X6.10
TEMP11: IC7.15, NTC_C11.1, NTC_R11.1, X6.12
TEMP12: IC12.1, NTC_C13.1, NTC_R13.1, X9.2
TEMP13: IC12.2, NTC_C14.1, NTC_R14.1, X9.6
TEMP14: IC12.12, NTC_C15.1, NTC_R15.1, X9.8
TEMP15: IC12.5, NTC_C16.1, NTC_R16.1, X9.4
TEMP16: IC12.14, NTC_C17.1, NTC_R17.1, X9.10
TEMP17: IC12.15, NTC_C20.1, NTC_R20.1, X9.12
TEMP18: IC13.1, NTC_C18.1, NTC_R18.1, X10.2
TEMP19: IC13.5, NTC_C19.1, NTC_R19.1, X10.4
TEMP20: IC13.2, NTC_C21.1, NTC_R21.1, X10.6
TEMP21: IC13.12, NTC_C24.1, NTC_R24.1, X10.8
TEMP22: IC13.14, NTC_C22.1, NTC_R22.1, X10.10
TEMP23: IC13.15, NTC_C23.1, NTC_R23.1, X10.12
TEMP24: IC19.1, NTC_C25.1, NTC_R25.1, X15.2
TEMP25: IC19.2, NTC_C26.1, NTC_R26.1, X15.6
TEMP26: IC19.12, NTC_C27.1, NTC_R27.1, X15.8
TEMP27: IC19.5, NTC_C28.1, NTC_R28.1, X15.4
TEMP28: IC19.14, NTC_C29.1, NTC_R29.1, X15.10
TEMP29: IC19.15, NTC_C32.1, NTC_R32.1, X15.12
TEMP30: IC20.1, NTC_C30.1, NTC_R30.1, X16.2
TEMP31: IC20.5, NTC_C31.1, NTC_R31.1, X16.4
TEMP32: IC20.2, NTC_C33.1, NTC_R33.1, X16.6
TEMP33: IC20.12, NTC_C36.1, NTC_R36.1, X16.8
TEMP34: IC20.14, NTC_C34.1, NTC_R34.1, X16.10
TEMP35: IC20.15, NTC_C35.1, NTC_R35.1, X16.12
TEMP36: IC26.1, NTC_C37.1, NTC_R37.1, X21.2
TEMP37: IC26.2, NTC_C38.1, NTC_R38.1, X21.6
TEMP38: IC26.12, NTC_C39.1, NTC_R39.1, X21.8
TEMP39: IC26.5, NTC_C40.1, NTC_R40.1, X21.4
TEMP40: IC26.14, NTC_C41.1, NTC_R41.1, X21.10
TEMP41: IC26.15, NTC_C44.1, NTC_R44.1, X21.12
TEMP42: IC27.1, NTC_C42.1, NTC_R42.1, X22.2
TEMP43: IC27.5, NTC_C43.1, NTC_R43.1, X22.4
TEMP44: IC27.2, NTC_C45.1, NTC_R45.1, X22.6
TEMP45: IC27.12, NTC_C48.1, NTC_R48.1, X22.8
TEMP46: IC27.14, NTC_C46.1, NTC_R46.1, X22.10
TEMP47: IC27.15, NTC_C47.1, NTC_R47.1, X22.12
TEMPR: C3.1, DT1.A, DT2.A, DT3.A, DT4.A, DT5.A, DT6.A, IC1.34, R9.1
TEMPR1: C28.1, DT7.A, DT8.A, DT9.A, DT10.A, DT11.A, DT12.A, IC3.34, R20.1
TEMPR2: C45.1, DT13.A, DT14.A, DT15.A, DT16.A, DT17.A, DT18.A, IC15.34, R34.1
TEMPR3: C61.1, DT19.A, DT20.A, DT21.A, DT22.A, DT23.A, DT24.A, IC22.34, R51.1
TS0: IC1.18, IC6.10, IC7.10
TS1: IC1.21, IC6.9, IC7.9
TS2: IC3.18, IC12.10, IC13.10
TS3: IC3.21, IC12.9, IC13.9
TS4: IC15.18, IC19.10, IC20.10
TS5: IC15.21, IC19.9, IC20.9
TS6: IC22.18, IC26.10, IC27.10
TS7: IC22.21, IC26.9, IC27.9
UCT1: IC1.30, IC6.3
UCT2: IC1.32, IC6.13
UCT3: IC1.35, IC7.3
UCT4: IC1.40, IC7.13
UCT5: IC3.40, IC13.13
UCT6: IC3.35, IC13.3
UCT7: IC3.32, IC12.13
UCT8: IC3.30, IC12.3
UCT9: IC15.40, IC20.13
UCT10: IC15.35, IC20.3
UCT11: IC15.32, IC19.13
UCT12: IC15.30, IC19.3
UCT13: IC22.40, IC27.13
UCT14: IC22.35, IC27.3
UCT15: IC22.32, IC26.13
UCT16: IC22.30, IC26.3
V+: C1.1, IC2.1, Q1.3, R59.2
V+1: C16.1, IC9.1, Q4.3, R14.2
V+2: C37.1, IC16.1, Q6.3, R30.2
V+3: C53.1, IC23.1, Q8.3, R47.2
V+S: D1.C, D2.C, Q1.2, RGQ1_1.1, V+R.2
V+S1: D3.C, D4.C, Q4.2, RGQ1_4.1, V+R1.2
V+S2: D5.C, D6.C, Q6.2, RGQ1_7.1, V+R2.2
V+S3: D7.C, D8.C, Q8.2, RGQ1_10.1, V+R3.2
VREF: CVREF.2, IC2.31
VREF1: CVREF1.2, IC9.31
VREF2: CVREF2.2, IC16.31
VREF3: CVREF3.2, IC23.31
VREG: CVREG.2, IC2.32
VREG1: CVREG1.2, IC9.32
VREG2: CVREG2.2, IC16.32
VREG3: CVREG3.2, IC23.32
XTALIN: C15.2, IC1.6, Y1.P3
XTALIN1: C11.2, IC3.6, Y2.P3
XTALIN2: C33.2, IC15.6, Y3.P3
XTALIN3: C50.2, IC22.6, Y4.P3
XTALOUT: C14.2, IC1.7, Y1.P1
XTALOUT1: C10.2, IC3.7, Y2.P1
XTALOUT2: C32.2, IC15.7, Y3.P1
XTALOUT3: C49.2, IC22.7, Y4.P1
